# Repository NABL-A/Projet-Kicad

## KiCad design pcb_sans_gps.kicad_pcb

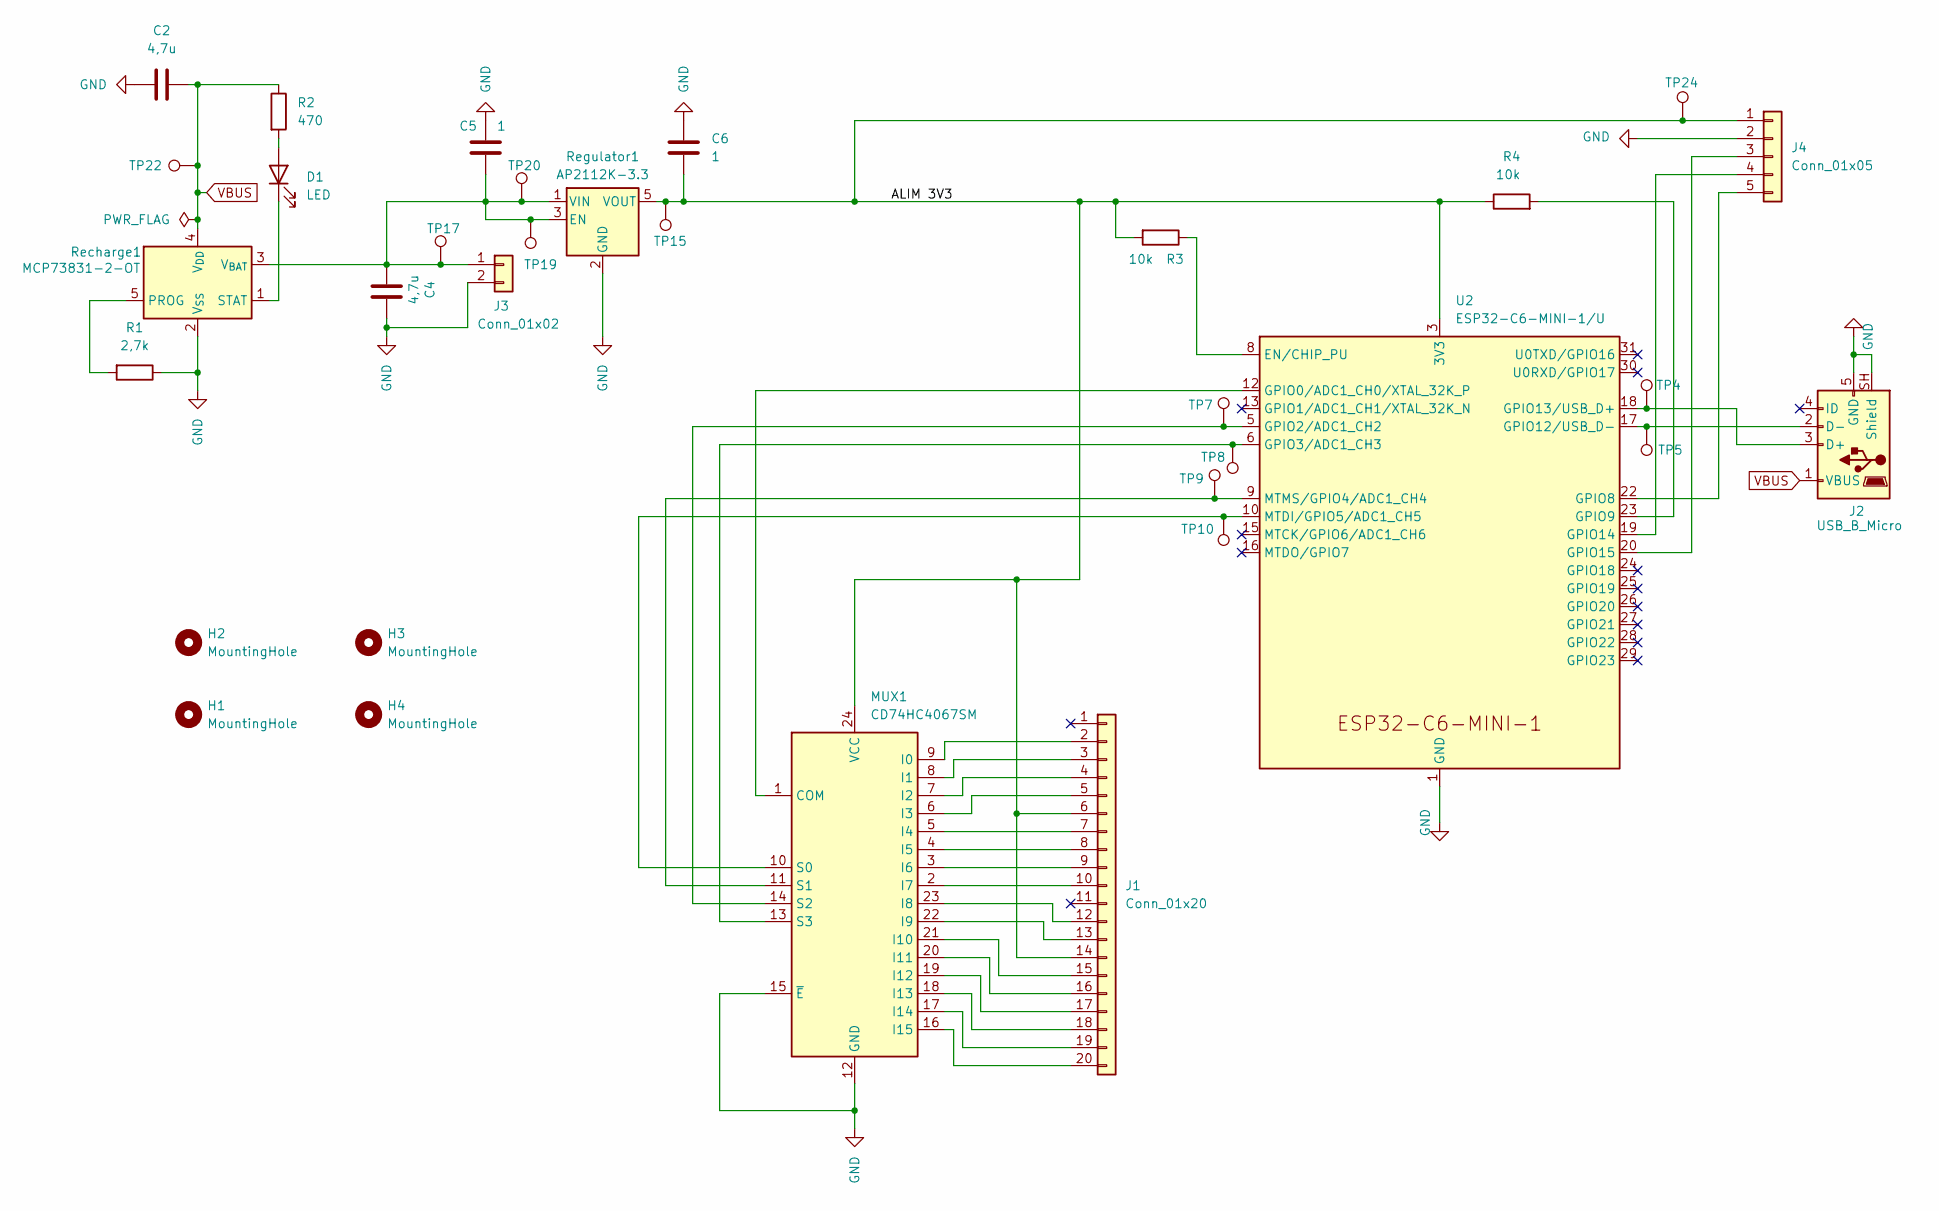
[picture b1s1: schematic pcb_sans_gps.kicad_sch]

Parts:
C2, C4: 4,7u; C_0603_1608Metric
C5, C6: 1; C_0603_1608Metric
D1: LED; D_0603_1608Metric
H1, H2, H3, H4: MountingHole; MountingHole_3.2mm_M3
J1: Conn_01x20; JUSHUO_AFA07-S20FCA-00_1x20-1MP_P1.0mm_Horizontal
J2: USB_B_Micro; USB_Micro-B_Amphenol_10103594-0001LF_Horizontal
J3: Conn_01x02; JST_PH_S2B-PH-K_1x02_P2.00mm_Horizontal
J4: Conn_01x05; PinSocket_1x05_P2.54mm_Vertical
MUX1: CD74HC4067SM; SSOP-24_5.3x8.2mm_P0.65mm
R1: 2,7k; R_0603_1608Metric
R2: 470; R_0603_1608Metric
R3, R4: 10k; R_0603_1608Metric
Recharge1: MCP73831-2-OT; SOT-23-5
Regulator1: AP2112K-3.3; SOT-23-5
TP4, TP5, TP7, TP8, TP9, TP10, TP15, TP17, TP19, TP20, TP22, TP24: TestPoint; TestPoint_Pad_D1.0mm
U2: ESP32-C6-MINI-1/U; ESP32-C6-MINI-1

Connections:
/ALIM 3V3: C6.2, J1.6, J1.14, J4.1, MUX1.24 (VCC), R3.2, R4.1, Regulator1.5 (VOUT), TP15.1 (1_1), TP24.1 (1_1), U2.3 (3V3)
GND: C2.1, C4.1, C5.1, C6.1, J2.5 (GND), J2.SH (Shield), J3.2, J4.2, MUX1.12 (GND), MUX1.15 (~E), R1.1, Recharge1.2 (V_{SS}), Regulator1.2 (GND), U2.1 (GND), U2.2 (GND), U2.11 (GND), U2.14 (GND), U2.36 (GND), U2.37 (GND), U2.38 (GND), U2.39 (GND), U2.40 (GND), U2.41 (GND), U2.42 (GND), U2.43 (GND), U2.44 (GND), U2.45 (GND), U2.46 (GND), U2.47 (GND), U2.48 (GND), U2.49 (GND), U2.50 (GND), U2.51 (GND), U2.52 (GND), U2.53 (GND)
unnamed: D1.2 (A), R2.2
unnamed: D1.1 (K), Recharge1.1 (STAT)
unnamed: J1.2, MUX1.9 (I0)
unnamed: J1.3, MUX1.8 (I1)
unnamed: J1.4, MUX1.7 (I2)
unnamed: J1.5, MUX1.6 (I3)
unnamed: J1.7, MUX1.5 (I4)
unnamed: J1.8, MUX1.4 (I5)
unnamed: J1.9, MUX1.3 (I6)
unnamed: J1.10, MUX1.2 (I7)
unnamed: J1.12, MUX1.23 (I8)
unnamed: J1.13, MUX1.22 (I9)
unnamed: J1.15, MUX1.21 (I10)
unnamed: J1.16, MUX1.20 (I11)
unnamed: J1.17, MUX1.19 (I12)
unnamed: J1.18, MUX1.18 (I13)
unnamed: J1.19, MUX1.17 (I14)
unnamed: J1.20, MUX1.16 (I15)
unnamed: J2.3 (D+), TP4.1 (1_1), U2.18 (GPIO13/USB_D+)
unnamed: J2.2 (D-), TP5.1 (1_1), U2.17 (GPIO12/USB_D-)
unnamed: C4.2, C5.2, J3.1, Recharge1.3 (V_{BAT}), Regulator1.1 (VIN), Regulator1.3 (EN), TP17.1 (1_1), TP19.1 (1_1), TP20.1 (1_1)
unnamed: J4.3, U2.20 (GPIO15)
unnamed: J4.4, U2.19 (GPIO14)
unnamed: J4.5, U2.22 (GPIO8)
unnamed: MUX1.1 (COM), U2.12 (GPIO0/ADC1_CH0/XTAL_32K_P)
unnamed: MUX1.10 (S0), TP10.1 (1_1), U2.10 (MTDI/GPIO5/ADC1_CH5)
unnamed: MUX1.11 (S1), TP9.1 (1_1), U2.9 (MTMS/GPIO4/ADC1_CH4)
unnamed: MUX1.14 (S2), TP7.1 (1_1), U2.5 (GPIO2/ADC1_CH2)
unnamed: MUX1.13 (S3), TP8.1 (1_1), U2.6 (GPIO3/ADC1_CH3)
unnamed: R1.2, Recharge1.5 (PROG)
unnamed: R3.1, U2.8 (EN/CHIP_PU)
unnamed: R4.2, U2.23 (GPIO9)
VBUS: C2.2, J2.1 (VBUS), R2.1, Recharge1.4 (V_{DD}), TP22.1 (1_1)

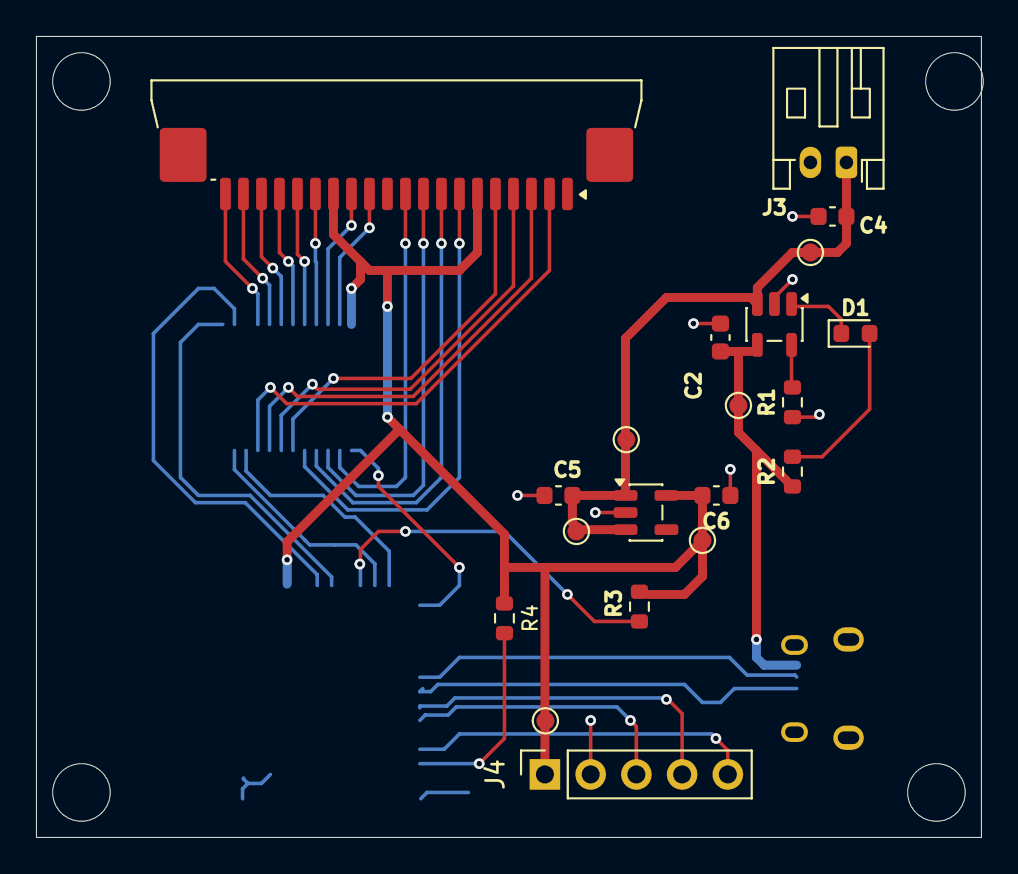
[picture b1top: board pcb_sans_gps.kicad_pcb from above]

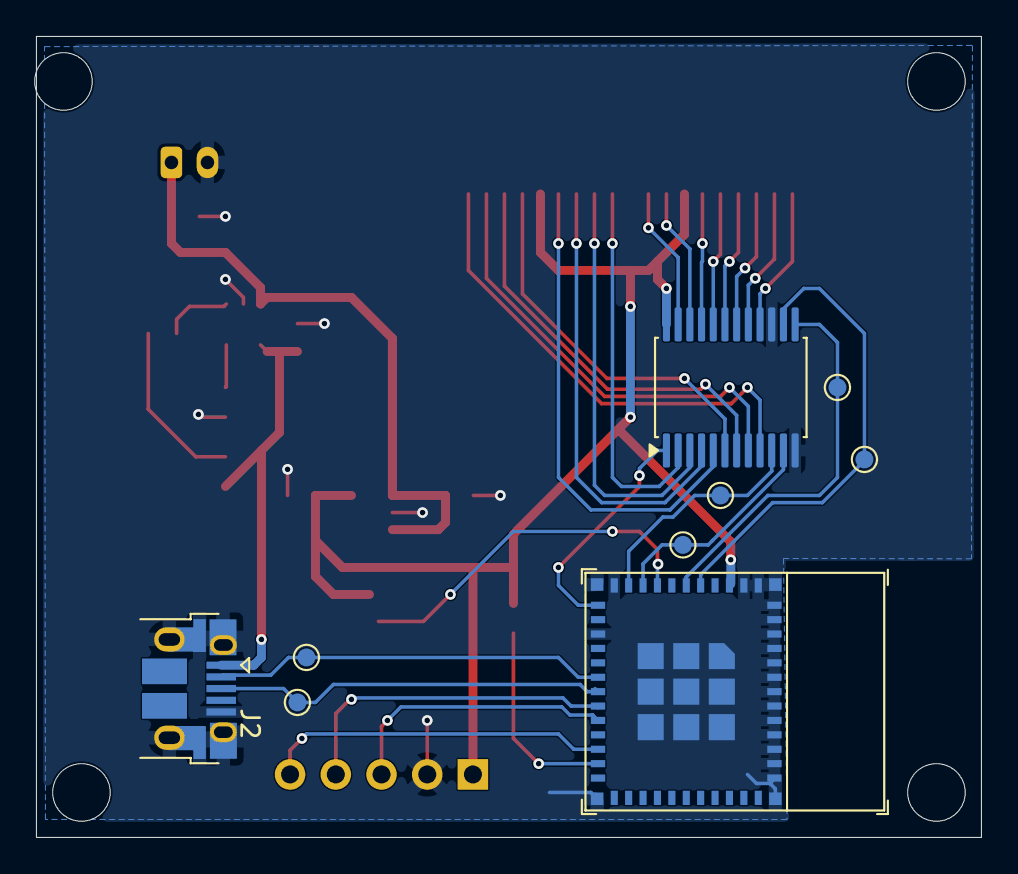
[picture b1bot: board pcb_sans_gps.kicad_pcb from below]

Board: 2 copper layers, 52.5 x 44.5 mm, 33 parts (9 on the bottom side), 35 nets.

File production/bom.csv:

Designator,Footprint,Quantity,Value,LCSC Part #
"C2, C4",603,2,"4,7u",
"C5, C6",603,2,1,
D1,603,1,LED,
J1,JUSHUO_AFA07-S20FCA-00_1x20-1MP_P1.0mm_Horizontal,1,Conn_01x20,C262724
J2,USB_Micro-B_Amphenol_10103594-0001LF_Horizontal,1,USB_B_Micro,C428495
J3,JST_PH_S2B-PH-K_1x02_P2.00mm_Horizontal,1,Conn_01x02,C173752
J4,PinSocket_1x05_P2.54mm_Vertical,1,Conn_01x05,C2897368
MUX1,SSOP-24_5.3x8.2mm_P0.65mm,1,CD74HC4067SM,C98457
R1,603,1,"2,7k",
R2,603,1,470,
"R3, R4",603,2,10k,
RECHARGE1,SOT-23-5,1,MCP73831-2-OT,C635036
REGULATOR1,SOT-23-5,1,AP2112K-3.3,C3021085
"TP10, TP15, TP17, TP19, TP20, TP22, TP24, TP4, TP5, TP7, TP8, TP9",TestPoint_Pad_D1.0mm,12,TestPoint,
U2,ESP32-C6-MINI-1,1,ESP32-C6-MINI-1/U,C5736265
